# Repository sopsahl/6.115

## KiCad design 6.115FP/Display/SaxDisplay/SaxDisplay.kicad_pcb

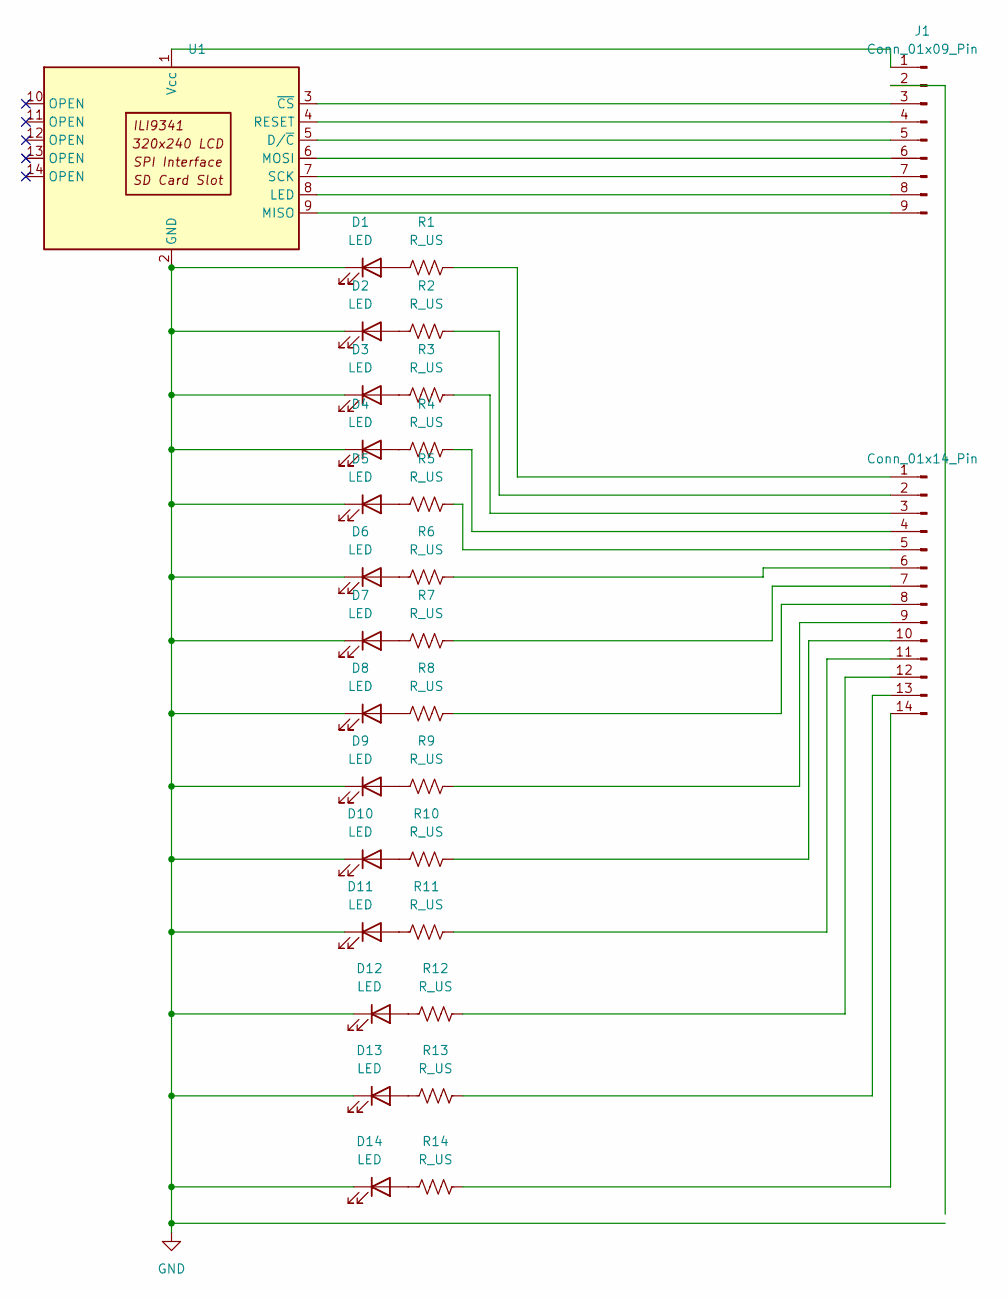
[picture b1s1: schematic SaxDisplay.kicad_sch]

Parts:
D1, D2, D3, D4, D5, D6, D7, D8, D9, D10, D11, D12, D13, D14: LED; LED_D3.0mm_Horizontal_O1.27mm_Z2.0mm
J1: Conn_01x09_Pin; PinSocket_1x09_P2.54mm_Vertical
J2: Conn_01x14_Pin; PinHeader_1x14_P2.54mm_Vertical
R1, R2, R3, R4, R5, R6, R7, R8, R9, R10, R11, R12, R13, R14: R_US; R_Axial_DIN0309_L9.0mm_D3.2mm_P12.70mm_Horizontal
U1: PinHeader_1x14_P2.54mm_Vertical

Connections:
GND: D1.1 (K), D2.1 (K), D3.1 (K), D4.1 (K), D5.1 (K), D6.1 (K), D7.1 (K), D8.1 (K), D9.1 (K), D10.1 (K), D11.1 (K), D12.1 (K), D13.1 (K), D14.1 (K), U1.2 (GND)
unnamed: D1.2 (A), R1.1
unnamed: D2.2 (A), R2.1
unnamed: D3.2 (A), R3.1
unnamed: D4.2 (A), R4.1
unnamed: D5.2 (A), R5.1
unnamed: D6.2 (A), R6.1
unnamed: D7.2 (A), R7.1
unnamed: D8.2 (A), R8.1
unnamed: D9.2 (A), R9.1
unnamed: D10.2 (A), R10.1
unnamed: D11.2 (A), R11.1
unnamed: D12.2 (A), R12.1
unnamed: D13.2 (A), R13.1
unnamed: D14.2 (A), R14.1
unnamed: J1.1, U1.1 (Vcc)
unnamed: J1.3, U1.3 (~CS)
unnamed: J1.4, U1.4 (RESET)
unnamed: J1.5, U1.5 (D/~C)
unnamed: J1.6, U1.6 (MOSI)
unnamed: J1.7, U1.7 (SCK)
unnamed: J1.8, U1.8 (LED)
unnamed: J1.9, U1.9 (MISO)
unnamed: J2.1, R1.2
unnamed: J2.2, R2.2
unnamed: J2.3, R3.2
unnamed: J2.4, R4.2
unnamed: J2.5, R5.2
unnamed: J2.6, R6.2
unnamed: J2.7, R7.2
unnamed: J2.8, R8.2
unnamed: J2.9, R9.2
unnamed: J2.10, R10.2
unnamed: J2.11, R11.2
unnamed: J2.12, R12.2
unnamed: J2.13, R13.2
unnamed: J2.14, R14.2

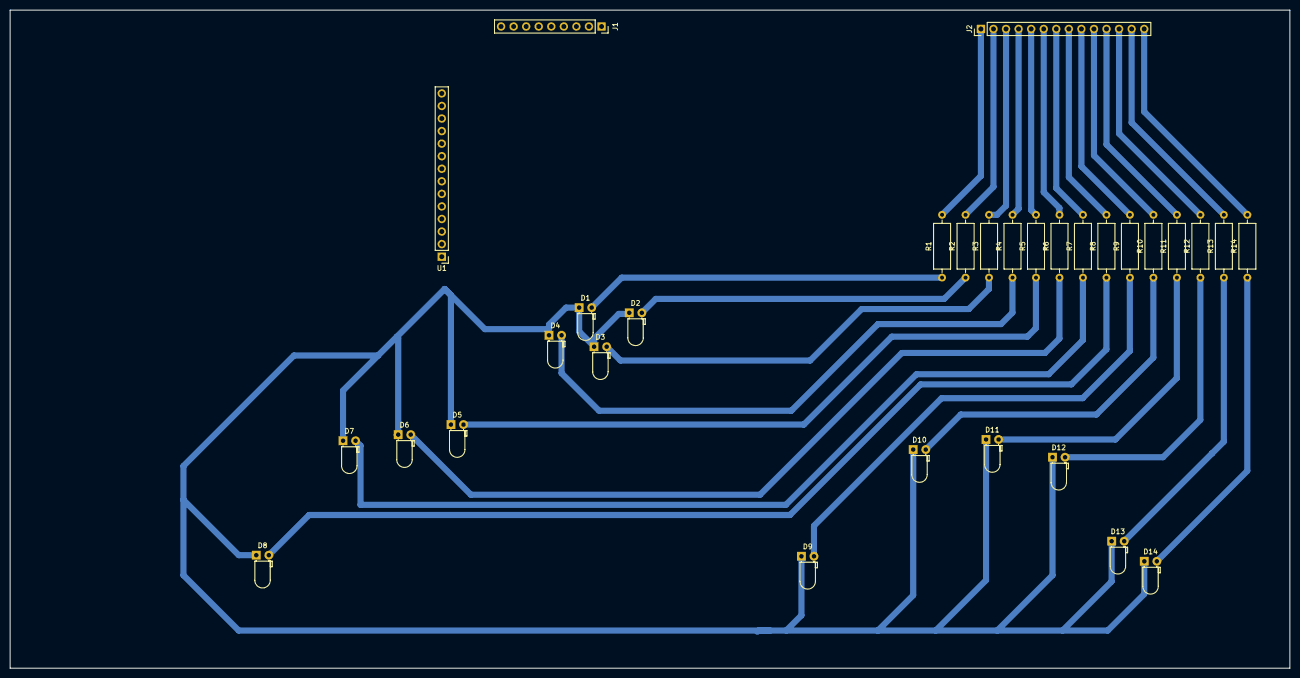
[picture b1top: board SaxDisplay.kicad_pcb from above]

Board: 2 copper layers, 258.8 x 133.1 mm, 31 parts (0 on the bottom side), 37 nets.

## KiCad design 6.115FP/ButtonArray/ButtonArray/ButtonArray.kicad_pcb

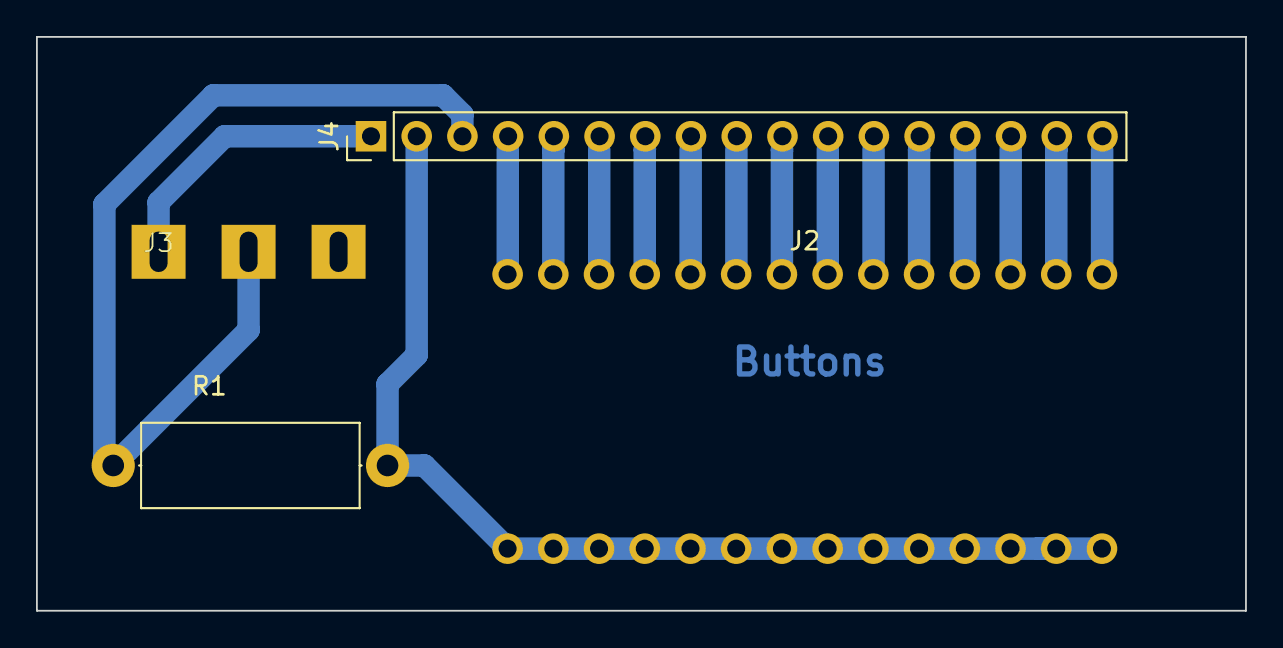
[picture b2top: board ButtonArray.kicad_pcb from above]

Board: 2 copper layers, 67.2 x 31.9 mm, 4 parts (0 on the bottom side), 17 nets.

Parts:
J2: Conn_02x14_Odd_Even; Samtec_HLE-114-02-xx-DV-PE_2x14_P2.54mm_Horizontal
J3: Conn_01x03_Pin; AHHH
J4: Conn_01x17_Pin; PinHeader_1x17_P2.54mm_Vertical
R1: 5 KOhm; R_Axial_DIN0414_L11.9mm_D4.5mm_P15.24mm_Horizontal

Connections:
+3.3V: J2.2, J2.4, J2.6, J2.8, J2.10, J2.12, J2.14, J2.16, J2.18, J2.20, J2.22, J2.24, J2.26, J2.28, J4.2, R1.2
unnamed: J2.1, J4.4
unnamed: J2.3, J4.5
unnamed: J2.5, J4.6
unnamed: J2.7, J4.7
unnamed: J2.9, J4.8
unnamed: J2.11, J4.9
unnamed: J2.13, J4.10
unnamed: J2.15, J4.11
unnamed: J2.17, J4.12
unnamed: J2.19, J4.13
unnamed: J2.21, J4.14
unnamed: J2.23, J4.15
unnamed: J2.25, J4.16
unnamed: J2.27, J4.17
unnamed: J3.1, J4.1
unnamed: J3.2, J4.3, R1.1

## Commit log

2024-04-30 Putting Files in
2024-04-30 UpdateStructure
2024-05-01 Sax Notes
2024-05-01 NewWaveforms
2024-05-15 Done
2024-05-15 All files Uploaded
2024-12-16 All final project work done
